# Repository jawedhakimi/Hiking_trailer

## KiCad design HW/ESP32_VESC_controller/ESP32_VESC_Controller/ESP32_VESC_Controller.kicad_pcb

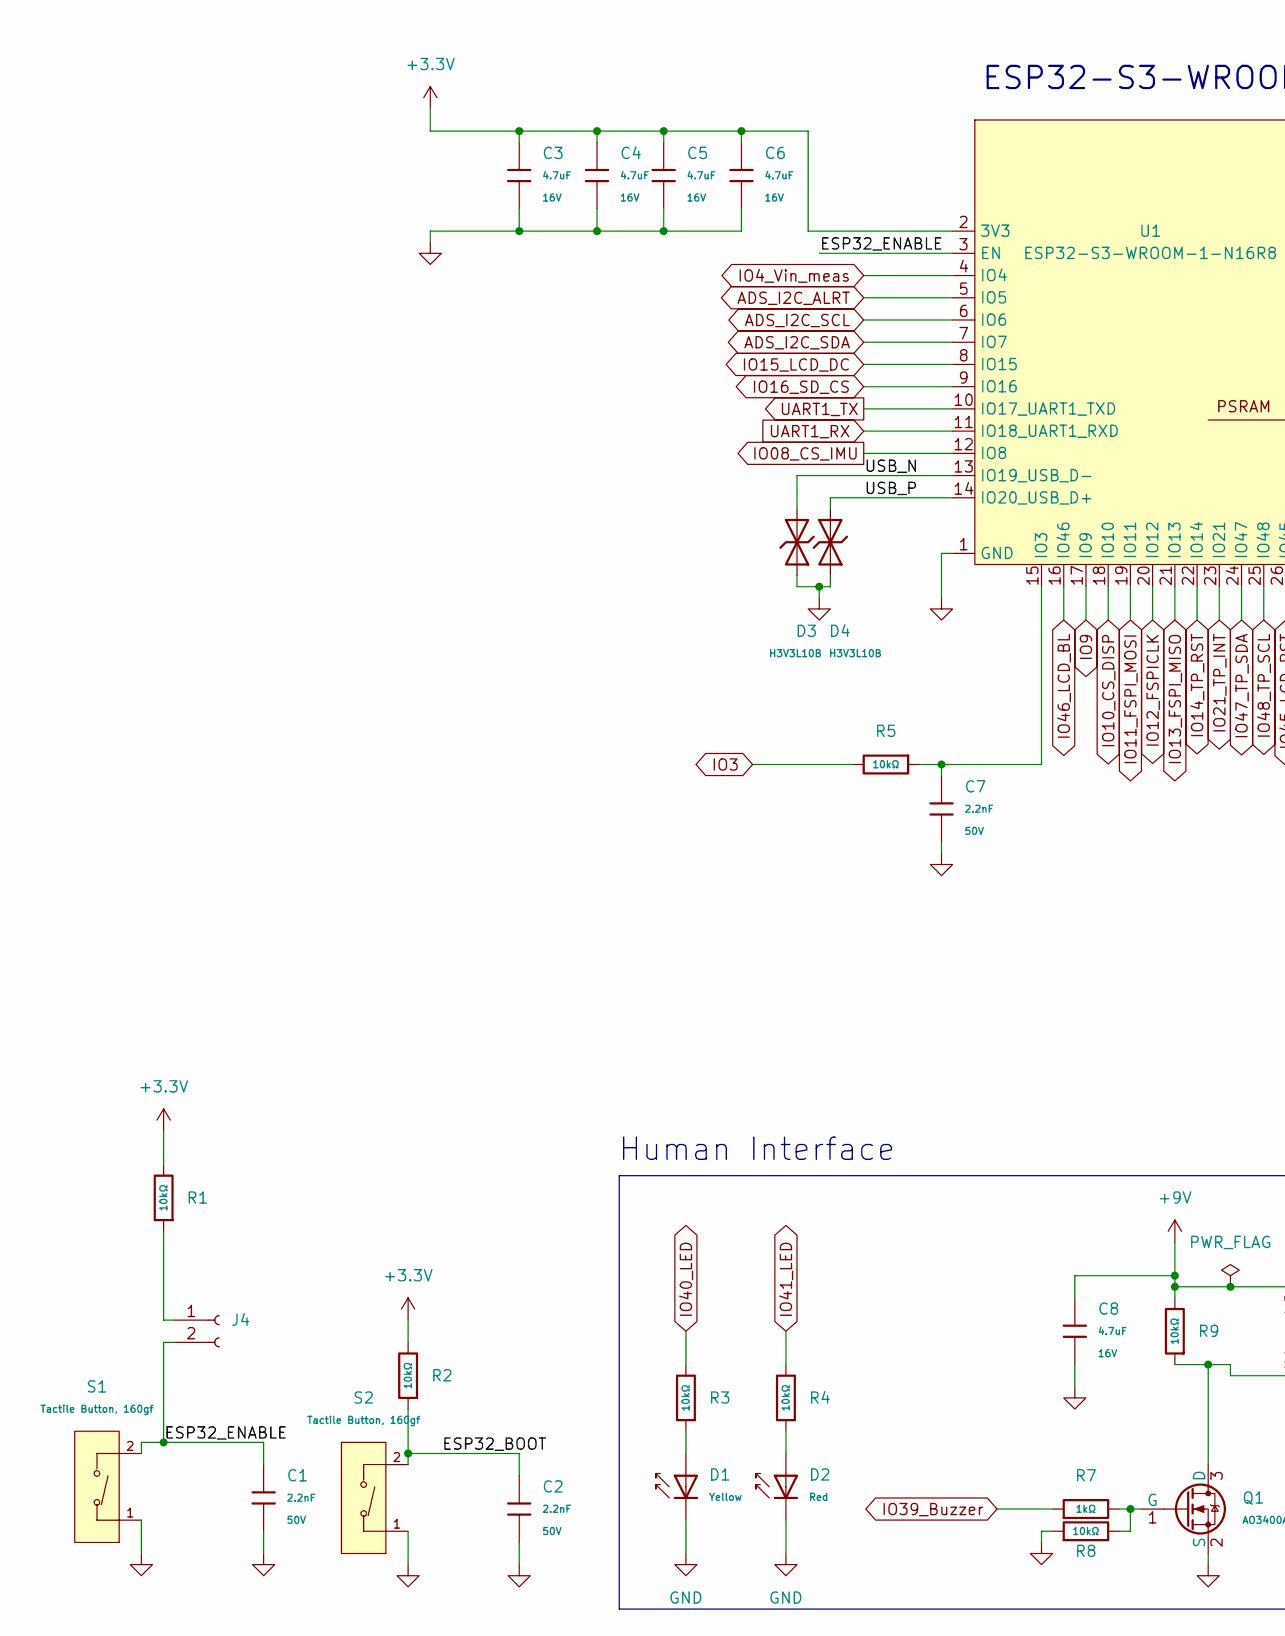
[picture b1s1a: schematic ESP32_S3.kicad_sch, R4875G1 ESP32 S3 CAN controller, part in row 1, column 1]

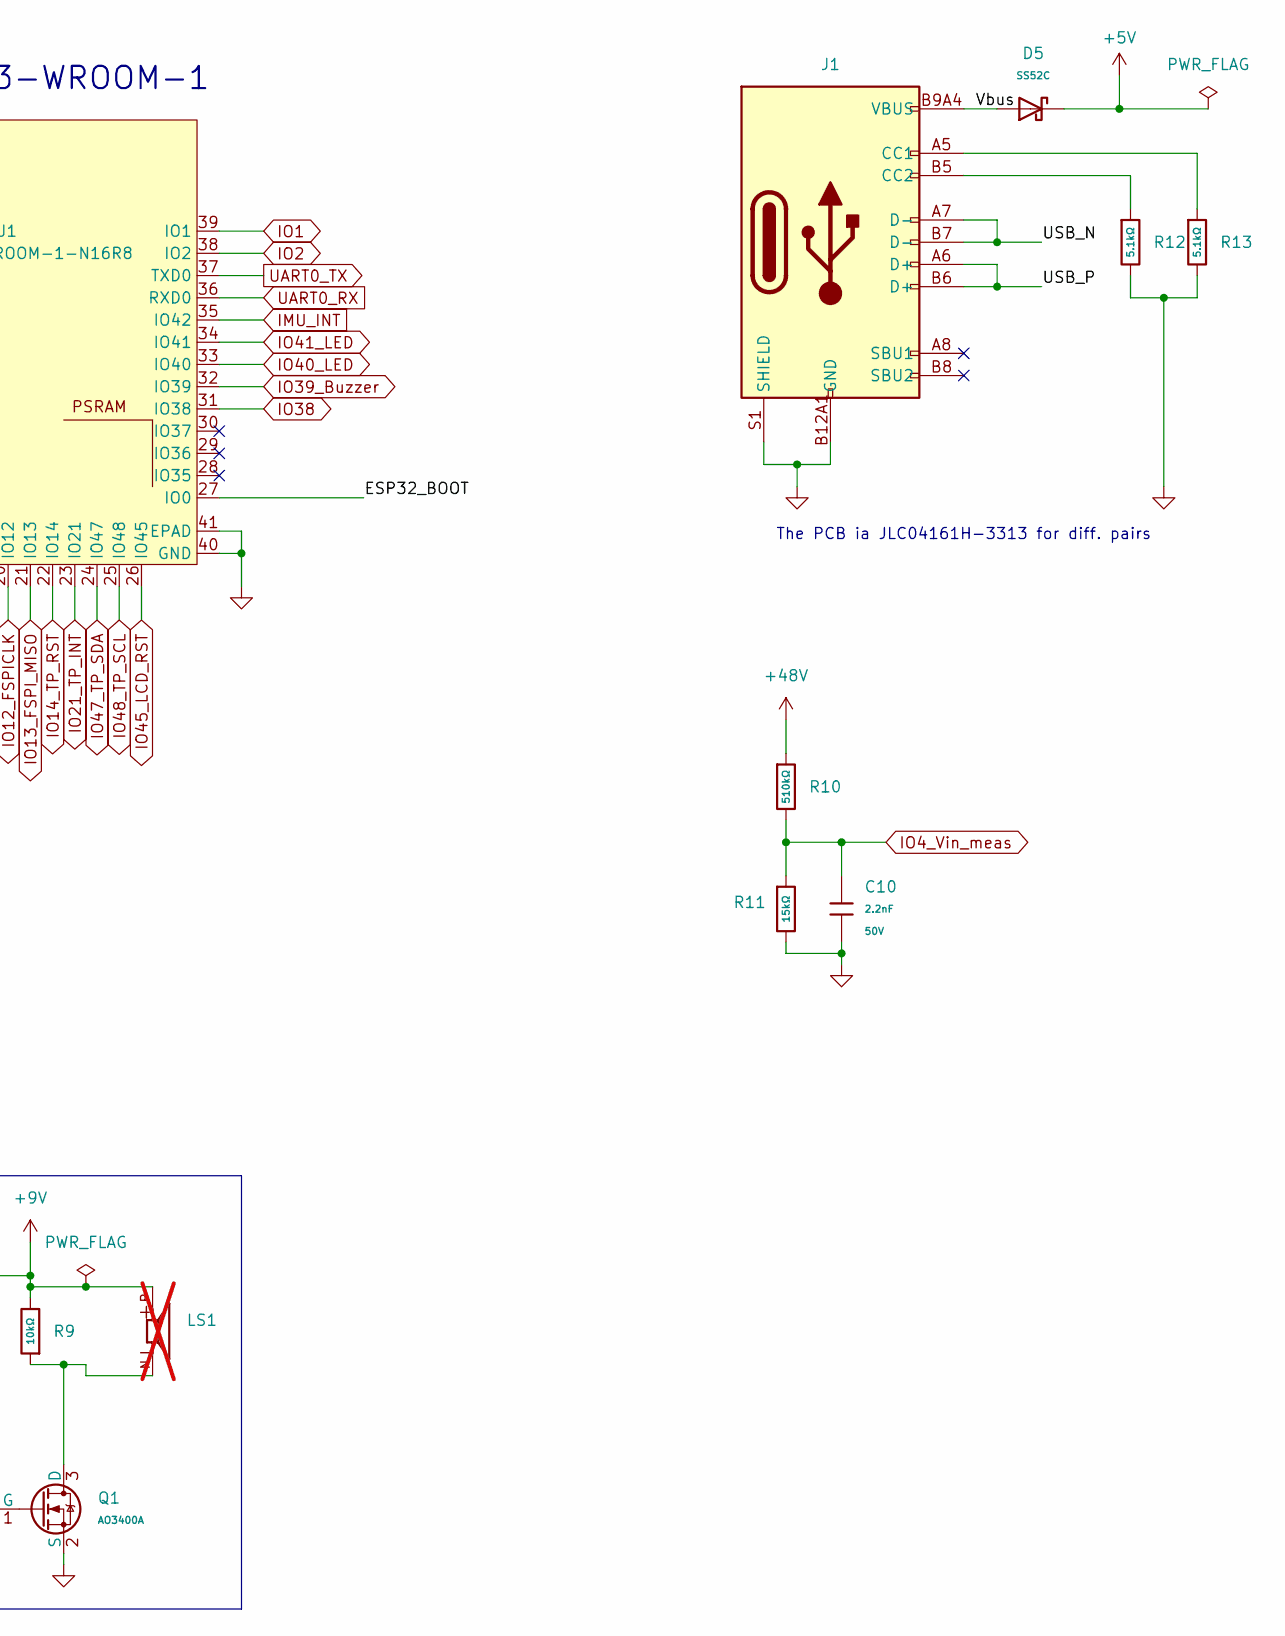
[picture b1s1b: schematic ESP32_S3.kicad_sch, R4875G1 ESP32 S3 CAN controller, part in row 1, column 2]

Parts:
C1, C2, C7, C10: 2.2nF; C_0402; Voltage Rated 50V; Tolerance ±10%; Part 0402B222K500NT; LCSC C1531
C3, C4, C5, C6, C8: 4.7uF; C_0603; Voltage Rated 16V; Tolerance ±10%; Part CL10A475KO8NNNC; LCSC C19666
D1: Yellow; D_0603; Forward Voltage (VF) 1.6V~2.6V; Part NCD0603Y2; LCSC C89811
D2: Red; D_0603; Part KT-0603R; LCSC C2286
D3, D4: H3V3L10B; D_DFN1006-2L; Breakdown Voltage 5.5V; Part H3V3L10B; LCSC C20615781
D5: SS52C; D_SMC; Voltage - Forward(Vf@If) 550mV@5.0A; Voltage - DC Reverse(Vr) 20V; Part SS52C; LCSC C41410784
J1: Connector, USB-TYPE-C-16P; TYPE-C-SMD_HX-TYPE-C-16PIN; LCSC C2927039
J4: Conn_01x02_Socket; PinHeader_1x02_P1.27mm_Vertical
LS1: PKLCS1212E4001-R1; SPKR_PKLCS1212E4001-R1; PARTREV January 22, 2018; not fitted
Q1: AO3400A; Q_SOT-23; Part AO3400A; LCSC C20917
R1, R2, R3, R4, R5, R8, R9: 10kΩ; R_0402; Overload Voltage (Max) 50V; Tolerance ±1%; Part 0402WGF1002TCE; LCSC C25744
R7: 1kΩ; R_0402; Overload Voltage (Max) 50V; Tolerance ±1%; Part 0402WGF1001TCE; LCSC C11702
R10: 510kΩ; R_0402; Overload Voltage (Max) 50V; Tolerance ±1%; Part 0402WGF5103TCE; LCSC C11616
R11: 15kΩ; R_0402; Overload Voltage (Max) 50V; Tolerance ±1%; Part 0402WGF1502TCE; LCSC C25756
R12, R13: 5.1kΩ; R_0402; Overload Voltage (Max) 50V; Tolerance ±1%; Part 0402WGF5101TCE; LCSC C25905
S1, S2: Tactile Button, 160gf; SW_TS-1088-AR02016; Voltage Rating (Dc) 12V; Part TS-1088-AR02016; LCSC C720477
U1: ESP32-S3-WROOM-1-N16R8; ESP32-S3-WROOM-1; JLCPCB Part# C2913202

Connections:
+3.3V: C3.1, C4.1, C5.1, C6.1, R1.2, R2.2, U1.2 (3V3); also elsewhere on the board
+5V: D5.1; also elsewhere on the board
+9V: C8.1, LS1.P, R9.2; also elsewhere on the board
+48V: R10.1; also elsewhere on the board
/ESP32_S3/ESP32_BOOT: C2.1, R2.1, S2.2 (B), U1.27 (IO0)
/ESP32_S3/ESP32_ENABLE: C1.1, J4.2, S1.2 (B), U1.3 (EN)
/ESP32_S3/USB_N: D3.1, J1.A7 (D-), J1.B7 (D-), U1.13 (IO19_USB_D-)
/ESP32_S3/USB_P: D4.2, J1.A6 (D+), J1.B6 (D+), U1.14 (IO20_USB_D+)
/ESP32_S3/Vbus: D5.2, J1.A9B4 (VBUS), J1.B9A4 (VBUS)
ADS_I2C_ALRT: U1.5 (IO5); also elsewhere on the board
ADS_I2C_SCL: U1.6 (IO6); also elsewhere on the board
ADS_I2C_SDA: U1.7 (IO7); also elsewhere on the board
GND: C1.2, C2.2, C3.2, C4.2, C5.2, C6.2, C7.2, C8.2, C10.2, D1.1, D2.1, D3.2, D4.1, J1.A12B1 (GND), J1.B12A1 (GND), J1.S1 (SHIELD), Q1.2 (S), R8.1, R11.2, R12.2, R13.2, S1.1 (A), S2.1 (A), U1.1 (GND), U1.40 (GND), U1.41 (EPAD); also elsewhere on the board
IMU_INT: U1.35 (IO42); also elsewhere on the board
IO1: U1.39 (IO1); also elsewhere on the board
IO2: U1.38 (IO2); also elsewhere on the board
IO3: R5.2; also elsewhere on the board
IO4_Vin_meas: C10.1, R10.2, R11.1, U1.4 (IO4)
IO08_CS_IMU: U1.12 (IO8); also elsewhere on the board
IO9: U1.17 (IO9); also elsewhere on the board
IO10_CS_DISP: U1.18 (IO10); also elsewhere on the board
IO11_FSPI_MOSI: U1.19 (IO11); also elsewhere on the board
IO12_FSPICLK: U1.20 (IO12); also elsewhere on the board
IO13_FSPI_MISO: U1.21 (IO13); also elsewhere on the board
IO14_TP_RST: U1.22 (IO14); also elsewhere on the board
IO15_LCD_DC: U1.8 (IO15); also elsewhere on the board
IO16_SD_CS: U1.9 (IO16); also elsewhere on the board
IO21_TP_INT: U1.23 (IO21); also elsewhere on the board
IO38: U1.31 (IO38); also elsewhere on the board
IO39_Buzzer: R7.1, U1.32 (IO39)
IO40_LED: R3.2, U1.33 (IO40); also elsewhere on the board
IO41_LED: R4.2, U1.34 (IO41); also elsewhere on the board
IO45_LCD_RST: U1.26 (IO45); also elsewhere on the board
IO46_LCD_BL: U1.16 (IO46); also elsewhere on the board
IO47_TP_SDA: U1.24 (IO47); also elsewhere on the board
IO48_TP_SCL: U1.25 (IO48); also elsewhere on the board
unnamed: D1.2, R3.1
unnamed: D2.2, R4.1
unnamed: J1.A5 (CC1), R13.1
unnamed: J1.B5 (CC2), R12.1
unnamed: J4.1, R1.1
unnamed: LS1.N, Q1.3 (D), R9.1
unnamed: Q1.1 (G), R7.2, R8.2
unnamed: C7.1, R5.1, U1.15 (IO3)
UART0_RX: U1.36 (RXD0); also elsewhere on the board
UART0_TX: U1.37 (TXD0); also elsewhere on the board
UART1_RX: U1.11 (IO18_UART1_RXD); also elsewhere on the board
UART1_TX: U1.10 (IO17_UART1_TXD); also elsewhere on the board

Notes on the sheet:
Human Interface
ESP32-S3-WROOM-1
The PCB ia JLC04161H-3313 for diff. pairs

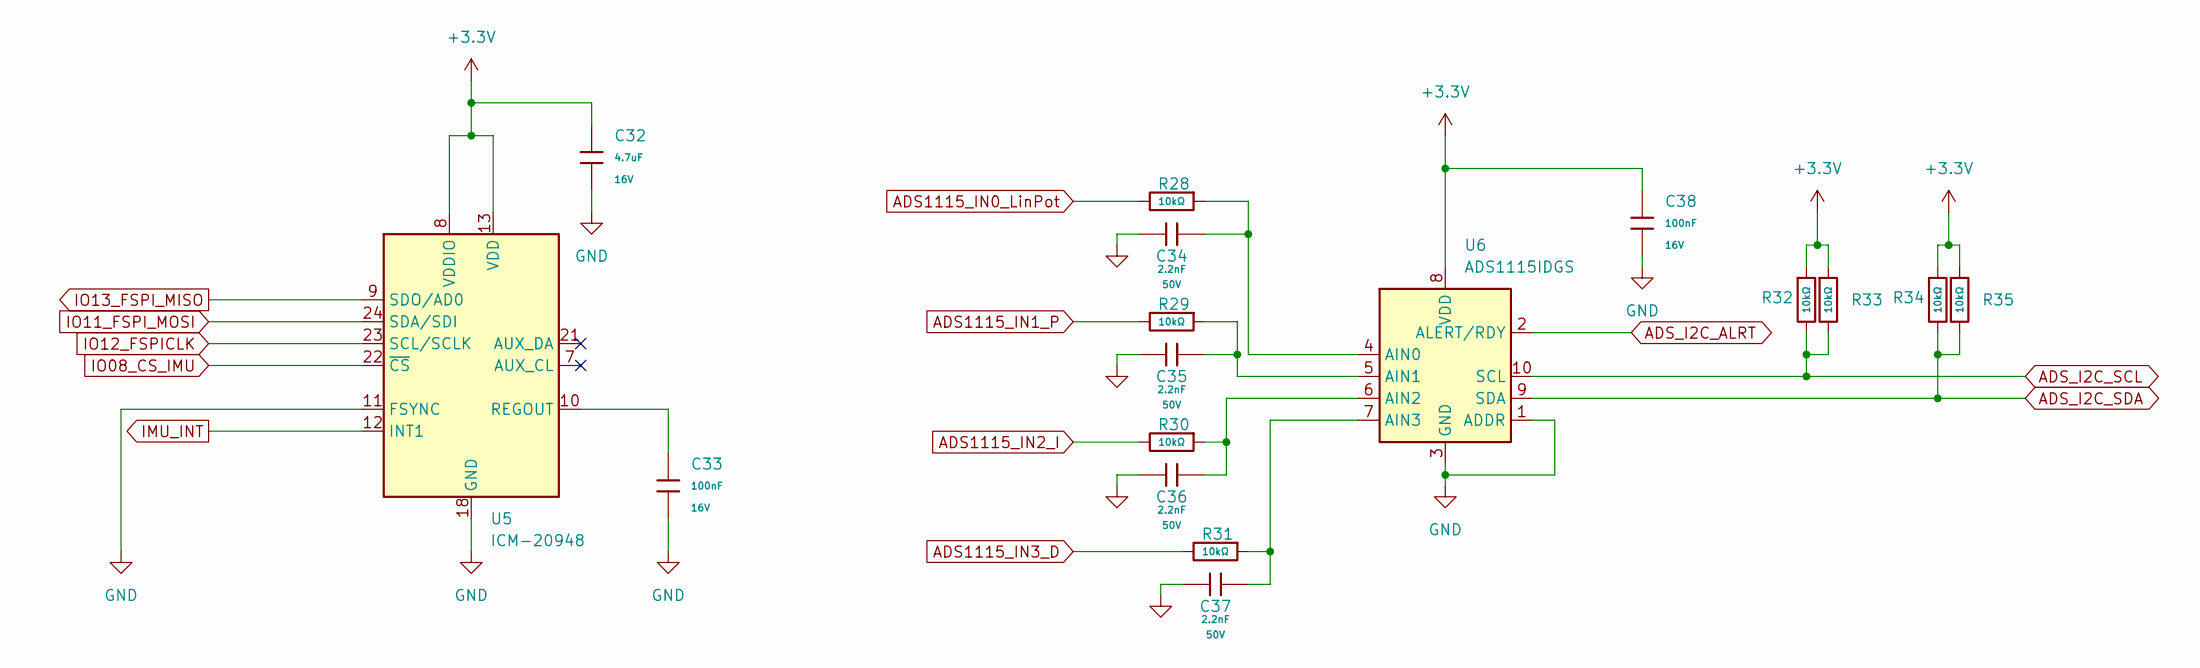
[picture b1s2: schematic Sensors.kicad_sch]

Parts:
C32: 4.7uF; C_0603; Voltage Rated 16V; Tolerance ±10%; Part CL10A475KO8NNNC; LCSC C19666
C33, C38: 100nF; C_0402; Voltage Rated 16V; Tolerance ±10%; Part CL05B104KO5NNNC; LCSC C1525
C34, C35, C36, C37: 2.2nF; C_0402; Voltage Rated 50V; Tolerance ±10%; Part 0402B222K500NT; LCSC C1531
R28, R29, R30, R31, R32, R33, R34, R35: 10kΩ; R_0402; Overload Voltage (Max) 50V; Tolerance ±1%; Part 0402WGF1002TCE; LCSC C25744
U5: ICM-20948; InvenSense_QFN-24_3x3mm_P0.4mm
U6: ADS1115IDGS; TSSOP-10_3x3mm_P0.5mm

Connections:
+3.3V: C32.1, C38.1, R32.1, R33.1, R34.1, R35.1, U5.8 (VDDIO), U5.13 (VDD), U6.8 (VDD); also elsewhere on the board
ADS1115_IN0_LinPot: R28.2; also elsewhere on the board
ADS1115_IN1_P: R29.2; also elsewhere on the board
ADS1115_IN2_I: R30.2; also elsewhere on the board
ADS1115_IN3_D: R31.2; also elsewhere on the board
ADS_I2C_ALRT: U6.2 (ALERT/RDY); also elsewhere on the board
ADS_I2C_SCL: R32.2, R33.2, U6.10 (SCL); also elsewhere on the board
ADS_I2C_SDA: R34.2, R35.2, U6.9 (SDA); also elsewhere on the board
GND: C32.2, C33.2, C34.2, C35.2, C36.2, C37.2, C38.2, U5.11 (FSYNC), U5.18 (GND), U5.20 (GND), U6.1 (ADDR), U6.3 (GND); also elsewhere on the board
IMU_INT: U5.12 (INT1); also elsewhere on the board
IO08_CS_IMU: U5.22 (~CS); also elsewhere on the board
IO11_FSPI_MOSI: U5.24 (SDA/SDI); also elsewhere on the board
IO12_FSPICLK: U5.23 (SCL/SCLK); also elsewhere on the board
IO13_FSPI_MISO: U5.9 (SDO/AD0); also elsewhere on the board
unnamed: C33.1, U5.10 (REGOUT)
unnamed: C34.1, R28.1, U6.4 (AIN0)
unnamed: C35.1, R29.1, U6.5 (AIN1)
unnamed: C36.1, R30.1, U6.6 (AIN2)
unnamed: C37.1, R31.1, U6.7 (AIN3)

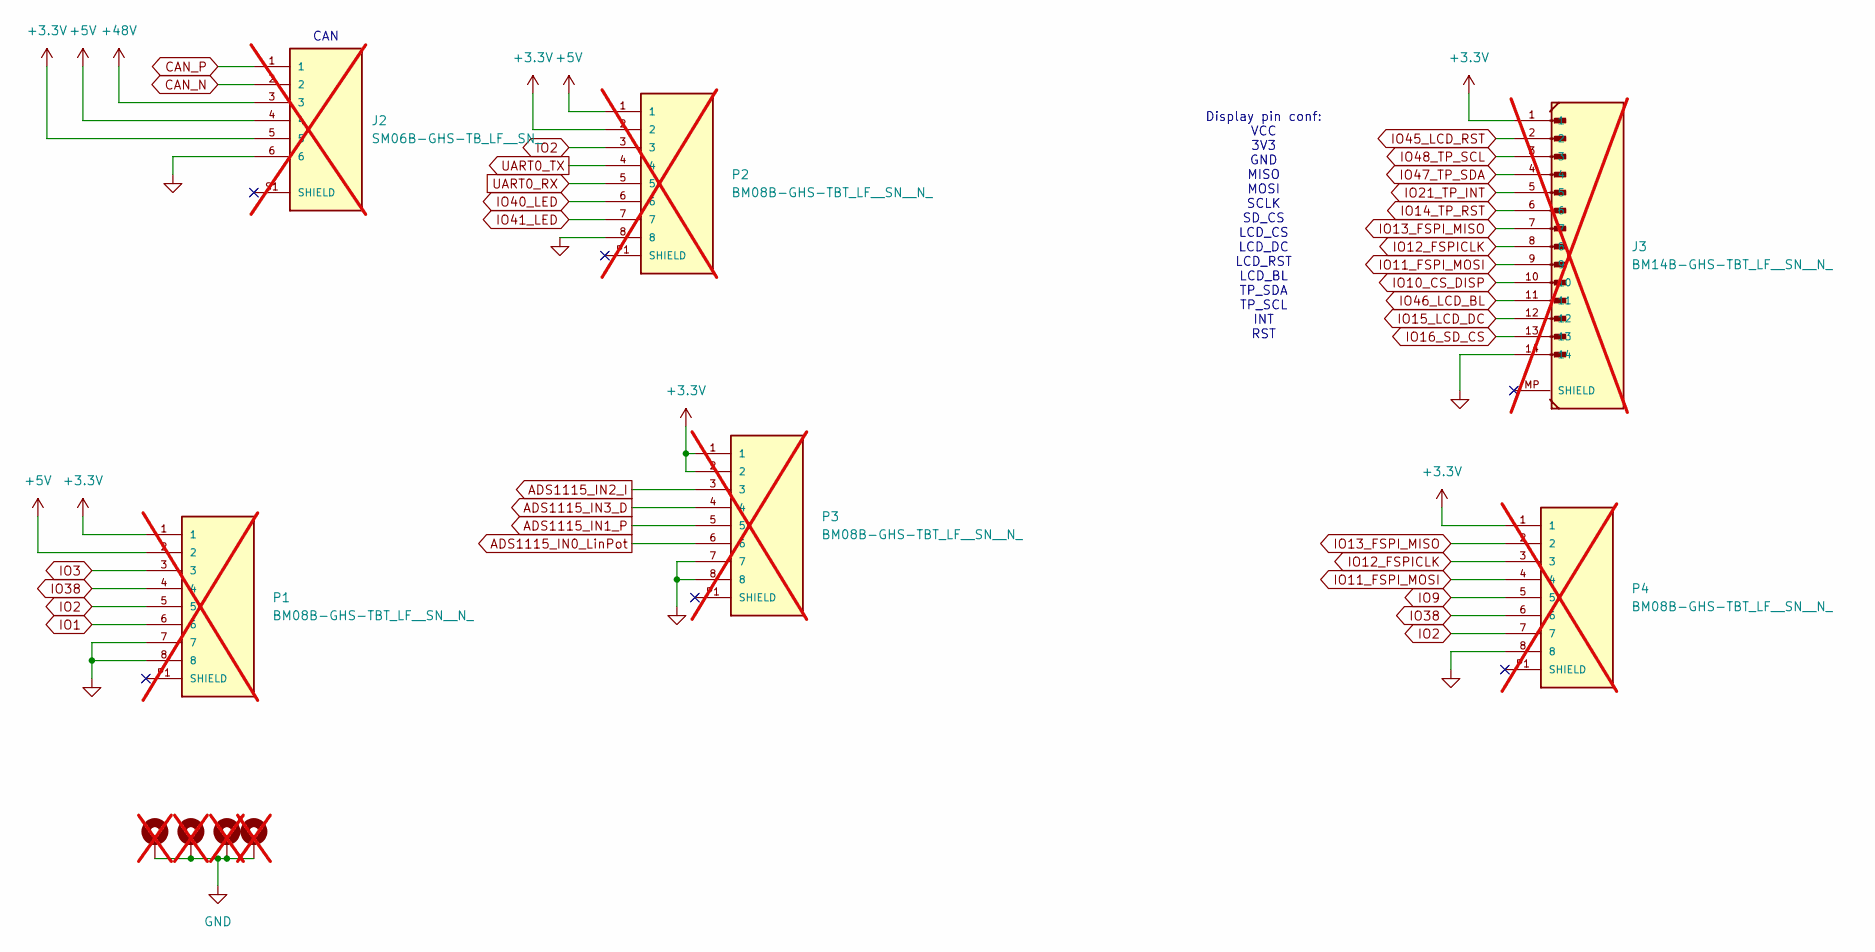
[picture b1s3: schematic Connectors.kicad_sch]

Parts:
H1, H2, H3, H4: MountingHole_Pad; MountingHole_2.7mm_M2.5_Pad; not fitted
J2: SM06B-GHS-TB_LF__SN_; JST_SM06B-GHS-TB_LF__SN_; PARTREV N/A; not fitted
J3: BM14B-GHS-TBT_LF__SN__N_; JST_GH_BM14B-GHS-TBT_1x14-1MP_P1.25mm_Vertical; PARTREV N/A; not fitted
P1, P2, P3, P4: BM08B-GHS-TBT_LF__SN__N_; JST_BM08B-GHS-TBT_LF__SN__N_; not fitted

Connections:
+3.3V: J2.5, J3.1, P1.1, P2.2, P3.1, P3.2, P4.1; also elsewhere on the board
+5V: J2.4, P1.2, P2.1; also elsewhere on the board
+48V: J2.3; also elsewhere on the board
ADS1115_IN0_LinPot: P3.6; also elsewhere on the board
ADS1115_IN1_P: P3.5; also elsewhere on the board
ADS1115_IN2_I: P3.3; also elsewhere on the board
ADS1115_IN3_D: P3.4; also elsewhere on the board
CAN_N: J2.2; also elsewhere on the board
CAN_P: J2.1; also elsewhere on the board
GND: H1.1 (1_1), H2.1 (1_1), H3.1 (1_1), H4.1 (1_1), J2.6, J3.14, P1.7, P1.8, P2.8, P3.7, P3.8, P4.8; also elsewhere on the board
IO1: P1.6; also elsewhere on the board
IO2: P1.5, P2.3, P4.7; also elsewhere on the board
IO3: P1.3; also elsewhere on the board
IO9: P4.5; also elsewhere on the board
IO10_CS_DISP: J3.10; also elsewhere on the board
IO11_FSPI_MOSI: J3.9, P4.4; also elsewhere on the board
IO12_FSPICLK: J3.8, P4.3; also elsewhere on the board
IO13_FSPI_MISO: J3.7, P4.2; also elsewhere on the board
IO14_TP_RST: J3.6; also elsewhere on the board
IO15_LCD_DC: J3.12; also elsewhere on the board
IO16_SD_CS: J3.13; also elsewhere on the board
IO21_TP_INT: J3.5; also elsewhere on the board
IO38: P1.4, P4.6; also elsewhere on the board
IO40_LED: P2.6; also elsewhere on the board
IO41_LED: P2.7; also elsewhere on the board
IO45_LCD_RST: J3.2; also elsewhere on the board
IO46_LCD_BL: J3.11; also elsewhere on the board
IO47_TP_SDA: J3.4; also elsewhere on the board
IO48_TP_SCL: J3.3; also elsewhere on the board
UART0_RX: P2.5; also elsewhere on the board
UART0_TX: P2.4; also elsewhere on the board

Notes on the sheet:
Display pin conf: VCC 3V3 GND MISO MOSI SCLK SD_CS LCD_CS LCD_DC LCD_RST LCD_BL TP_SDA TP_SCL INT RST
CAN

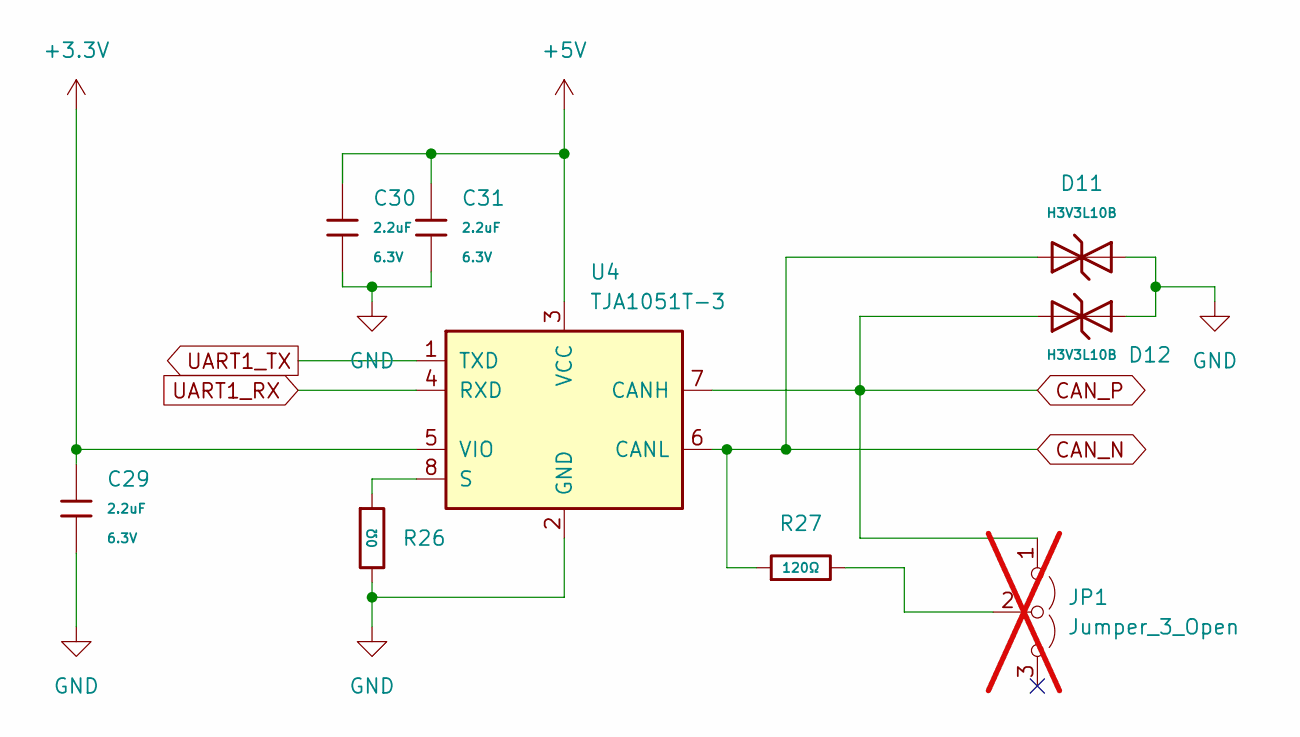
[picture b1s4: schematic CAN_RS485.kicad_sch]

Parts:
C29, C30, C31: 2.2uF; C_0402; Voltage Rated 6.3V; Tolerance ±20%; Part CL05A225MQ5NSNC; LCSC C12530
D11, D12: H3V3L10B; D_DFN1006-2L; Breakdown Voltage 5.5V; Part H3V3L10B; LCSC C20615781
JP1: Jumper_3_Open; SolderJumper-3_P1.3mm_Open_RoundedPad1.0x1.5mm_NumberLabels; not fitted
R26: 0Ω; R_0402; Overload Voltage (Max) 50V; Tolerance ±1%; Part 0402WGF0000TCE; LCSC C17168
R27: 120Ω; R_1206; Overload Voltage (Max) 200V; Tolerance ±1%; Part 1206W4F1200T5E; LCSC C17909
U4: TJA1051T-3; SOIC-8_3.9x4.9mm_P1.27mm

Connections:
+3.3V: C29.1, U4.5 (VIO); also elsewhere on the board
+5V: C30.1, C31.1, U4.3 (VCC); also elsewhere on the board
CAN_N: D11.2, R27.1, U4.6 (CANL); also elsewhere on the board
CAN_P: D12.1, JP1.1 (A), U4.7 (CANH); also elsewhere on the board
GND: C29.2, C30.2, C31.2, D11.1, D12.2, R26.2, U4.2 (GND); also elsewhere on the board
unnamed: JP1.2 (C), R27.2
unnamed: R26.1, U4.8 (S)
UART1_RX: U4.4 (RXD); also elsewhere on the board
UART1_TX: U4.1 (TXD); also elsewhere on the board

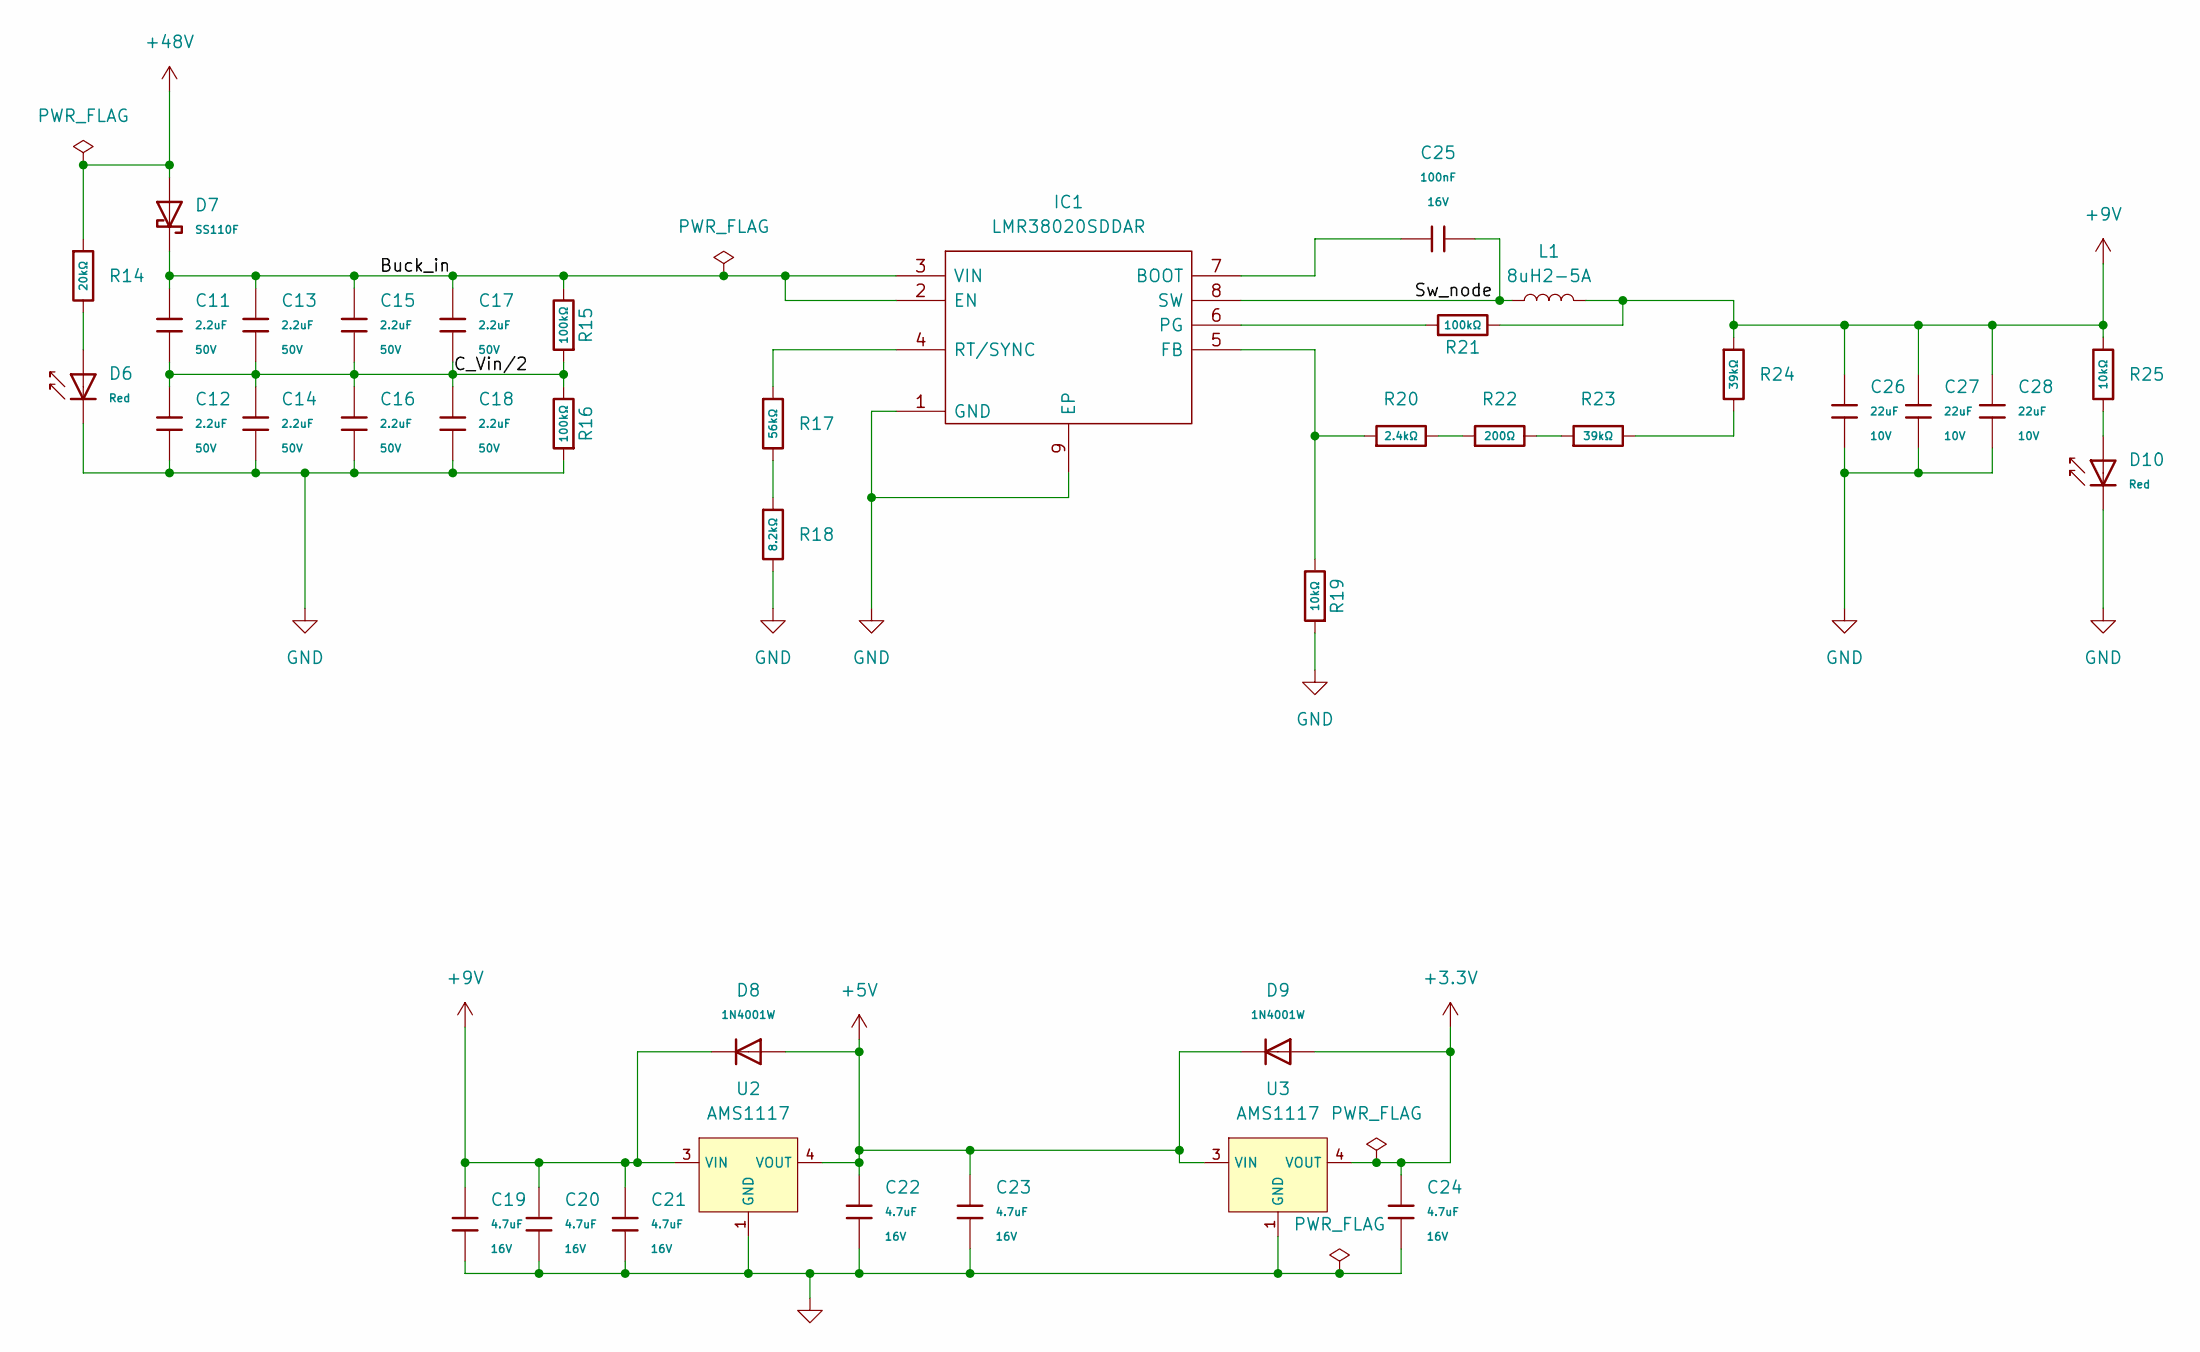
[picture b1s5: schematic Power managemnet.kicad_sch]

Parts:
C11, C12, C13, C14, C15, C16, C17, C18: 2.2uF; C_0805; Voltage Rated 50V; Tolerance ±10%; Part CL21A225KBQNNNE; LCSC C377773
C19, C20, C21, C22, C23, C24: 4.7uF; C_0603; Voltage Rated 16V; Tolerance ±10%; Part CL10A475KO8NNNC; LCSC C19666
C25: 100nF; C_0402; Voltage Rated 16V; Tolerance ±10%; Part CL05B104KO5NNNC; LCSC C1525
C26, C27, C28: 22uF; C_1206; Voltage Rated 10V; Tolerance ±10%; Part CL31A226KPHNNNE; LCSC C5672
D6, D10: Red; D_0603; Part KT-0603R; LCSC C2286
D7: SS110F; D_SMAF; Forward Voltage (Vf@If) 850mV@1A; Reverse Voltage (Vr) 100V; Part SS110F; LCSC C41411770
D8, D9: 1N4001W; D_SOD-123FL; Voltage - Forward(Vf@If) 1V@1.0A; Voltage - DC Reverse(Vr) 50V; Part 1N4001W; LCSC C18199085
IC1: LMR38020SDDAR; SOIC127P600X170-9N; Manufacturer_Part_Number LMR38020SDDAR; Mouser Part Number 595-LMR38020SDDAR
L1: 8uH2-5A; IND-SMD_L6.0-W6.0; JLCPCB Part# C167222
R14: 20kΩ; R_0402; Overload Voltage (Max) 50V; Tolerance ±1%; Part 0402WGF2002TCE; LCSC C25765
R15, R16, R21: 100kΩ; R_0402; Overload Voltage (Max) 50V; Tolerance ±1%; Part 0402WGF1003TCE; LCSC C25741
R17: 56kΩ; R_0402; Overload Voltage (Max) 50V; Tolerance ±1%; Part 0402WGF5602TCE; LCSC C25796
R18: 8.2kΩ; R_0402; Overload Voltage (Max) 50V; Tolerance ±1%; Part 0402WGF8201TCE; LCSC C25924
R19, R25: 10kΩ; R_0402; Overload Voltage (Max) 50V; Tolerance ±1%; Part 0402WGF1002TCE; LCSC C25744
R20: 2.4kΩ; R_0402; Overload Voltage (Max) 50V; Tolerance ±1%; Part 0402WGF2401TCE; LCSC C25882
R22: 200Ω; R_0402; Overload Voltage (Max) 50V; Tolerance ±1%; Part 0402WGF2000TCE; LCSC C25087
R23, R24: 39kΩ; R_0402; Overload Voltage (Max) 50V; Tolerance ±1%; Part 0402WGF3902TCE; LCSC C25783
U2: AMS1117; SOT-223_L6.5-W3.5-P2.30-LS7.0-BR; Output Voltage 5V; Dropout Voltage 1.3V@(1A); Part AMS1117-5.0; LCSC C6187
U3: AMS1117; SOT-223-3_L6.5-W3.4-P2.30-LS7.0-BR; Output Voltage 3.3V; Dropout Voltage 1.3V@(800mA); Part AMS1117-3.3; LCSC C6186

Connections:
+3.3V: C24.1, D9.2, U3.2 (VOUT), U3.4 (VOUT); also elsewhere on the board
+5V: C22.1, C23.1, D8.2, D9.1, U2.2 (VOUT), U2.4 (VOUT), U3.3 (VIN); also elsewhere on the board
+9V: C19.1, C20.1, C21.1, C26.1, C27.1, C28.1, D8.1, L1.2, R21.2, R24.1, R25.2, U2.3 (VIN); also elsewhere on the board
+48V: D7.2, R14.1; also elsewhere on the board
/Power managemnet/Buck_in: C11.1, C13.1, C15.1, C17.1, D7.1, IC1.2 (EN), IC1.3 (VIN), R15.2
/Power managemnet/C_Vin/2: C11.2, C12.1, C13.2, C14.1, C15.2, C16.1, C17.2, C18.1, R15.1, R16.2
/Power managemnet/Sw_node: C25.2, IC1.8 (SW), L1.1
GND: C12.2, C14.2, C16.2, C18.2, C19.2, C20.2, C21.2, C22.2, C23.2, C24.2, C26.2, C27.2, C28.2, D6.1, D10.1, IC1.1 (GND), IC1.9 (EP), R16.1, R18.2, R19.1, U2.1 (GND), U3.1 (GND); also elsewhere on the board
unnamed: D6.2, R14.2
unnamed: D10.2, R25.1
unnamed: C25.1, IC1.7 (BOOT)
unnamed: IC1.5 (FB), R19.2, R20.1
unnamed: IC1.6 (PG), R21.1
unnamed: IC1.4 (RT/SYNC), R17.1
unnamed: R17.2, R18.1
unnamed: R20.2, R22.1
unnamed: R22.2, R23.1
unnamed: R23.2, R24.2

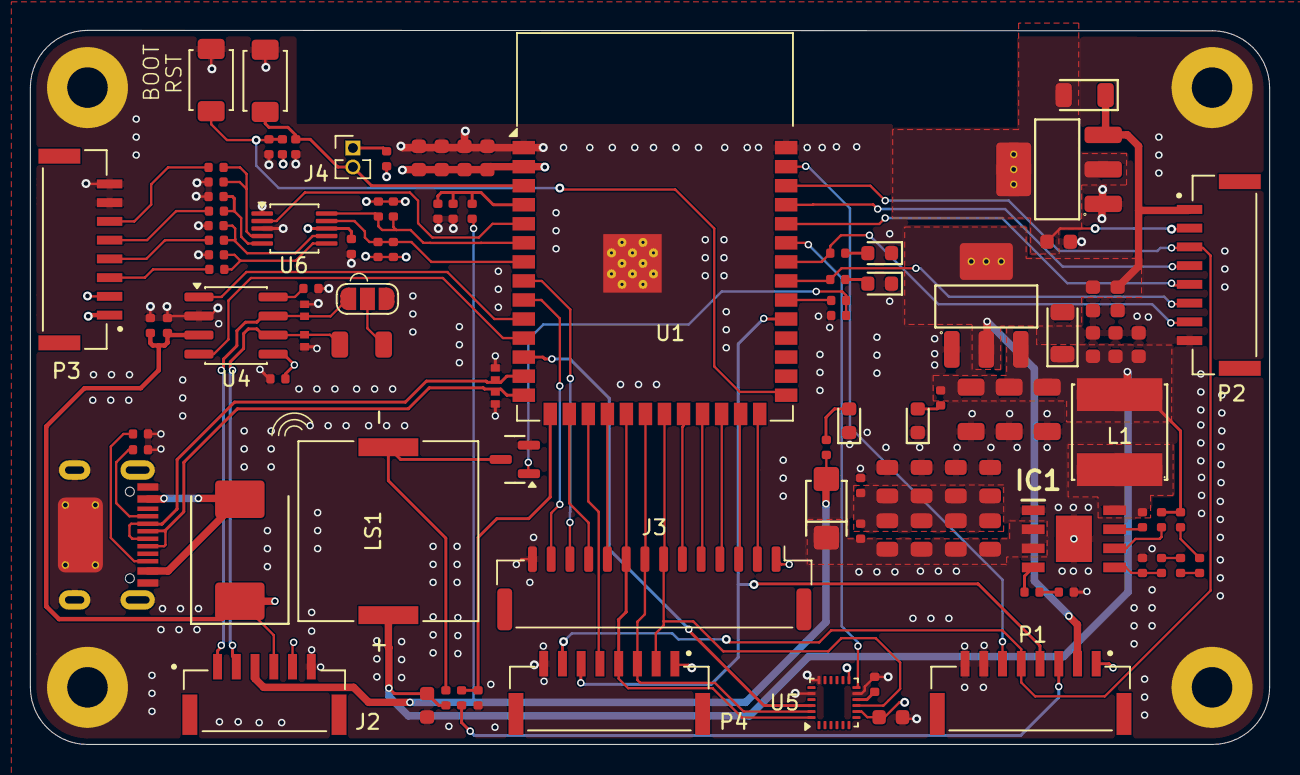
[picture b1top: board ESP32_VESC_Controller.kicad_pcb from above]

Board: 4 copper layers, 82.6 x 47.6 mm, 108 parts (0 on the bottom side), 74 nets.
